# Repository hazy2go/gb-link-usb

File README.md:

<h1 align="center">gb-link-usb</h1>

<p align="center">
  <strong>Connect a Game Boy's link port to your computer over USB.</strong><br>
  Print from a real Game Boy straight to PNG, or watch live crypto prices from SODAX on it,<br>
  with a Raspberry Pi Pico 2 W and one cut link cable.
</p>

<p align="center">

</p>

<p align="center">
  <a href="#quick-start">Quick start</a> ·
  <a href="#printing">Printing</a> ·
  <a href="#sodax-on-the-game-boy">SODAX</a> ·
  <a href="#troubleshooting">Troubleshooting</a> ·
  <a href="#how-it-works">How it works</a> ·
  <a href="#roadmap">Roadmap</a>
</p>

---

## Highlights

- **A Game Boy Printer that saves PNGs.** The Pico answers exactly like Nintendo's printer, so games print as usual, and every picture lands on your computer.
- **Live SODAX market data on the Game Boy.** Prices, charts and real swap quotes from the [SODAX](https://sodax.com) API, drawn by our own Game Boy ROM.
- **No level shifter, no soldering.** The Pico 2's RP2350 pins tolerate the Game Boy's 5 V signals, so four wires on a breadboard are enough.
- **Double-click to use.** On a Mac, one launcher saves every print to `Pictures/GameBoy Prints`, with a sound. Any computer with Chrome or Edge can use the web page instead.
- **Tested and documented.** The printer logic and the decoder have automated tests, and every hardware step, measurement and bug is written down in the [logbook](docs/LOGBOOK.md).

## What you need

| | Part | Notes |
|---|---|---|
| 1 | **Raspberry Pi Pico 2 W** (or 2 WH) | Must be a Pico **2**. An original Pico (RP2040) is not 5 V tolerant and needs a level shifter. |
| 2 | **Game Boy link cable** you can cut | Built and tested with a DMG-04. You keep one plug end. |
| 3 | Breadboard and jumper wires | Or solder the four wires straight to the Pico. |
| 4 | Multimeter with continuity beep | To find which wire is which: colours are not standard. |
| 5 | Mac with [Node.js](https://nodejs.org), or any computer with Chrome/Edge | For saving the prints. |

## Quick start

### 1. Map the cable

Cut the link cable, keep one plug with some cable attached, and strip the wire ends. With the multimeter in beep mode, put a paperclip in one plug hole and touch each wire until it beeps.

| Plug pin | Signal | Pico pin |
|:---:|---|:---:|
| 5 | SCK, clock | **1** (GP0) |
| 2 | SOUT, data from the Game Boy | **2** (GP1) |
| 6 | GND | **3** (GND) |
| 3 | SIN, data to the Game Boy | **4** (GP2) |

Pins 1 (5 V) and 4 (SD) are usually not in the cable and are not needed. Leave the bare shield unconnected and taped.

### 2. Wire it to the Pico

<table>
  <tr>
    <td width="42%"></td>
    <td>
      <p>Press the Pico into the middle of the breadboard, USB end up. Each cable wire goes into a free hole in the same row as its Pico pin, on the left side of the gap.</p>
      <p>Nothing else is connected: no level shifter, no power wires.</p>
      <p>Hole-by-hole drawing: <a href="https://hazy2go.github.io/gb-link-usb/breadboard.html">interactive wiring page</a>.</p>
      <blockquote><strong>Power order matters.</strong> Plug the Pico into USB <em>before</em> switching the Game Boy on, and switch the Game Boy off <em>before</em> unplugging the Pico. The RP2350 tolerates 5 V on its pins only while it is powered.</blockquote>
    </td>
  </tr>
</table>

### 3. Flash the firmware

1. Get `gb_link_usb.uf2` from [Releases](../../releases), or [build it yourself](#development).
2. Hold the white **BOOTSEL** button on the Pico while plugging it into USB, then let go. A drive called **RP2350** appears.
3. Drag `gb_link_usb.uf2` onto the drive. The Pico restarts as a Game Boy Printer.

## Printing

### On a Mac: double-click

1. Download this repository (**Code → Download ZIP**) and unzip it.
2. Double-click **`GB Printer.command`**. The first time, macOS may block it: right-click it → **Open** → **Open**.
3. Wait for `Pico connected`, then print from the game.

Every print is saved in **Pictures → GameBoy Prints**, at original size and at 4×, with a sound. Unplugging and replugging the Pico is fine. Leave the window open while you print.

### Any computer: the web page

Open **<https://hazy2go.github.io/gb-link-usb/>** in Chrome or Edge, click **Connect Pico**, and print. Prints appear on the page with a PNG download link. Nothing to install.

<sub>To run it locally instead: `cd web && python3 -m http.server 8000`, then open http://localhost:8000.</sub>

## SODAX on the Game Boy

<p align="center"><sub>Emulator screenshots with live data. Tested on a real DMG.</sub></p>

Live prices, a 24H / 7D / 30D chart and a **real swap quote from the SODAX solver** for 9 coins (BTC, ETH, SOL, SODA, SUI, HYPE, AVAX, XLM, POL), on an original Game Boy.

1. Put `sodax.gb` (from [Releases](../../releases)) on a flash cart such as an EverDrive.
2. With the Pico on USB, double-click **`SODAX Bridge.command`** (or run `node tools/sodax-bridge.mjs`). Close the print tool first: one program uses the Pico at a time.
3. Switch the Game Boy on and start `sodax.gb`.

| Button | Action |
|---|---|
| ◄ ► (or ▲ ▼) | previous / next coin |
| B | time range: 24H, 7D, 30D |
| A or Start | load fresh data now (it also refreshes every 30 s) |

Prices come from the SODAX oracle (`/oracle/candles`), quotes from the SODAX solver (`/intent/quote`), no API key needed. How the Game Boy, the Pico's bridge mode and the PC talk: [`docs/SODAX.md`](docs/SODAX.md).

## Troubleshooting

| Problem | What to check |
|---|---|
| The game reports a printer error | Wiring: beep each plug pin to its Pico pin. If your colours were mapped wrong, swap the two data wires (plug pins 2 and 3). Power order: Pico first. |
| Stuck on `Waiting for the Pico...` | Is the printer firmware on the Pico? It should appear as **Pico** by Raspberry Pi. Try another USB cable, some are charge-only. |
| A print did not save | See `gbprint.log` in the prints folder. Raw data of every session is kept in `raw/`; `node tools/render.mjs <file>` turns it into PNGs. |
| SODAX screen stays on "waiting" | Is the bridge window open and saying "bridge mode on"? Is the Pico on firmware v0.2.0 or newer? Press A to request a screen. |
| The web page cannot connect | Use Chrome or Edge on a desktop (Safari and Firefox have no Web Serial). Close the Mac tool first: only one program can use the Pico at a time. |

## How it works

```
Game Boy link port ──► Pico 2 W ──────────────────────────────────────► computer
 5 V, clocked serial    PIO follows the Game Boy's clock (glitch filter)    gbprint.mjs or the web page
                        core 1: answers like a Game Boy Printer             decodes packets → PNG
                        core 0: streams every byte over USB serial
```

- **Link layer.** A PIO state machine is the clock *slave*: it outputs a bit when the Game Boy's clock falls and samples the Game Boy's bit when it rises. A 1.6 µs glitch filter rejects crosstalk from the data line, which otherwise shows up as extra clock edges.
- **Printer.** [`firmware/src/printer.c`](firmware/src/printer.c) replies `0x00` to every byte, then the printer ID `0x81` and a status byte, and walks through the same status sequence as a real printer (busy while "printing", then ready). Replies are queued two bytes ahead, matching how the PIO loads them.
- **Decoding.** [`web/gbprinter.js`](web/gbprinter.js) parses packets, checks checksums, expands compressed data, turns 2-bit tiles into pixels and applies the print palette. The same file runs in the browser and in the Mac tool.

*Right: a test image sent through the full printer protocol and decoded by that code.*

<br clear="right">

## Project layout

```
firmware/         Pico 2 W firmware (C, Pico SDK): PIO link, printer emulator, USB serial
  test/           host tests for the printer state machine
  firstlight/     patch used to run stacksmashing's firmware for the first wiring test
web/              decoder library + web page (Web Serial)
tools/            gbprint.mjs (Mac print tool), sodax-bridge.mjs + sodax.mjs (SODAX data),
                  render.mjs, printcap.py, linktest.py
rom/              Game Boy ROMs (RGBDS): sodax.gb, linktest.gb, printtest.gb; mkfont.py makes the font
hw/              own PCB (KiCad, rev A ready to order), case, scripted build + checks
sim/link/        ngspice simulation of the link lines
docs/             PROTOCOL.md, PLAN.md, PCB.md, LOGBOOK.md, breadboard drawing, images
GB Printer.command    double-click launcher for the Mac print tool
SODAX Bridge.command  double-click launcher for SODAX on the Game Boy
```

## Development

```sh
# firmware (needs the Arm GNU toolchain and Pico SDK 2.3.1; PICO_SDK_PATH set)
cmake -S firmware -B firmware/build -G Ninja && ninja -C firmware/build   # → firmware/build/gb_link_usb.uf2

# tests
make -C firmware/test        # printer state machine (host, with sanitizers)
cd web && npm test           # decoder

# Game Boy ROMs (RGBDS)
make -C rom
node tools/sodax-bridge.mjs --dry   # print live SODAX screens without hardware
```

`rom/printtest.gb` makes the Game Boy act like a printing game and shows on screen what the printer answers (`… 81 00` is correct). `rom/linktest.gb` echoes bytes for testing the link in the other direction. Details: [`firmware/README.md`](firmware/README.md).

## Roadmap

- [x] Wiring and first link test: 1,000 bytes both ways, 0 errors
- [x] Game Boy Printer emulator: prints from a DMG saved as PNG
- [ ] More printer games tested (compressed and multi-part prints)
- [x] General PC link: live SODAX market data on the Game Boy (bridge mode)
- [ ] Online link play between two Game Boys
- [ ] Own small PCB with USB-C and a case, so nobody has to cut a cable: rev A designed and checked ([hw/](hw/README.md)), not ordered yet

## Credits

- [Pan Docs](https://gbdev.io/pandocs/): link port and printer documentation.
- [mofosyne/arduino-gameboy-printer-emulator](https://github.com/mofosyne/arduino-gameboy-printer-emulator): the reference printer emulator. Our printer status behaviour follows it; the code is our own.
- [stacksmashing/gb-link-firmware](https://github.com/stacksmashing/gb-link-firmware): Pico link firmware, used with a small patch for the first wiring test.
- [SODAX](https://sodax.com): market data API and the official logo used on the splash screen (from [gosodax/sodax-sdks](https://github.com/gosodax/sodax-sdks), MIT).
- [HerrZatacke/gb-printer-web](https://github.com/HerrZatacke/gb-printer-web) and [Raphael-Boichot/The-TinyGB-Printer](https://github.com/Raphael-Boichot/The-TinyGB-Printer): prior art for printer images.

Sister project: [WiFi Game Boy Cartridge](https://github.com/hazy2go/wifi-game-boy-cartridge).

## License

[MIT](LICENSE). Exception: `firmware/firstlight/` patches GPL-3.0 code and is GPL-3.0.

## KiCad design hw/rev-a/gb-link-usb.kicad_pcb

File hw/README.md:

# Hardware: PCB rev A

A small USB-C dongle with the Game Boy link cable soldered on. RP2350A core from Raspberry Pi's minimal design, three 74LVC1T45 translators running the Game Boy side at USB 5 V (safe in any power order), ESD on USB and on the link lines. 34.2 x 63.7 mm, 2 layers, all parts on top, assembled by JLC. Spec and part choice: [`docs/PCB.md`](../docs/PCB.md). **Not ordered yet:** see [`rev-a/fab/ORDER.md`](rev-a/fab/ORDER.md).

Gerbers as the fab sees them (rendered independently with tracespace, top and bottom):

## Files
- `rev-a/`: KiCad 10 project. `link.json` is the source of the Link sheet (USB-C, buffers, ESD, cable pads, LED); the root sheet is Raspberry Pi's minimal design, edited by script.
- `rev-a/fab/`: order files (Gerbers zip, BOM, CPL) and the check reports.
- `case/`: 3D-printable case (OpenSCAD).
- `reference/RPI-RP2350A-MINIMAL_R4-S1_public/`: Raspberry Pi RP2350A minimal design (MIT, see its LICENSE.txt), the base for our board.
- `../sim/link/`: ngspice simulation of the link lines (why the series resistors are 220R with 100 pF).

## Rebuild everything (scripted, from the untouched RPi design)
KPY = KiCad's Python (`/Applications/KiCad/KiCad.app/Contents/Frameworks/Python.framework/Versions/Current/bin/python3`).
```sh
$KPY hw/tools/add_sheet.py          # schematic: root from RPi's design + Link sheet from link.json
$KPY hw/tools/extract_libs.py       # RPi symbols/footprints into project libraries
$KPY hw/tools/pcb_build.py          # board: RPi layout, new outline, our parts placed
$KPY hw/tools/pcb_route.py hand     # hand routes (GPIO fan, DIR lines)
$KPY hw/tools/pcb_gnd.py            # a GND via for every new GND pad
$KPY hw/tools/pcb_route.py 60       # Freerouting (retries until DRC is clean) + tidy-up + zone fill
hw/tools/make_fab.sh                # Gerbers, drill, BOM + check, CPL + check, pin audit
```

## Checks (all scripted, results 2026-10-16)
| check | tool | result |
|---|---|---|
| ERC | kicad-cli | same as Raspberry Pi's untouched design (2 off-grid, 1 power pin pair, 2 regulator pins) |
| DRC + schematic parity | kicad-cli | 0 errors, 0 warnings, 0 unconnected, parity 0 |
| Routing tidy-up | `route_audit.py` / `route_clean.py` | no stubs, sharp angles or pointless vias (one harmless detour on B_SI); a few sub-0.05 mm pad-entry jogs left (most in RPi's own routing, kept as drawn) |
| Part heights | `height_check.py` | tallest: USB-C 3.25 mm, buttons 2.5 mm (feeds the case) |
| Link signals | `sim/link/run_sim.py` | 0 of 72 runs over a limit or glitching with 220R + 100 pF (SIN: 1k, also clean) |
| Independent review | fresh agent, datasheets only | no wiring defect; findings fixed or listed (LOGBOOK 2026-10-16) |
| BOM vs JLC | `make_bom.py` | all parts exist, match footprint and value; 1 stock FAIL: L1 inductor (hold point) |
| Placement | `make_cpl.py` | all 57 parts matched pad by pad against JLC's footprints |
| Pins | `pin_audit.py` | every pin vs JLC's symbol; caught the LED's reversed pad numbering (fixed in the CPL) |
| Gerbers | tracespace | render above |

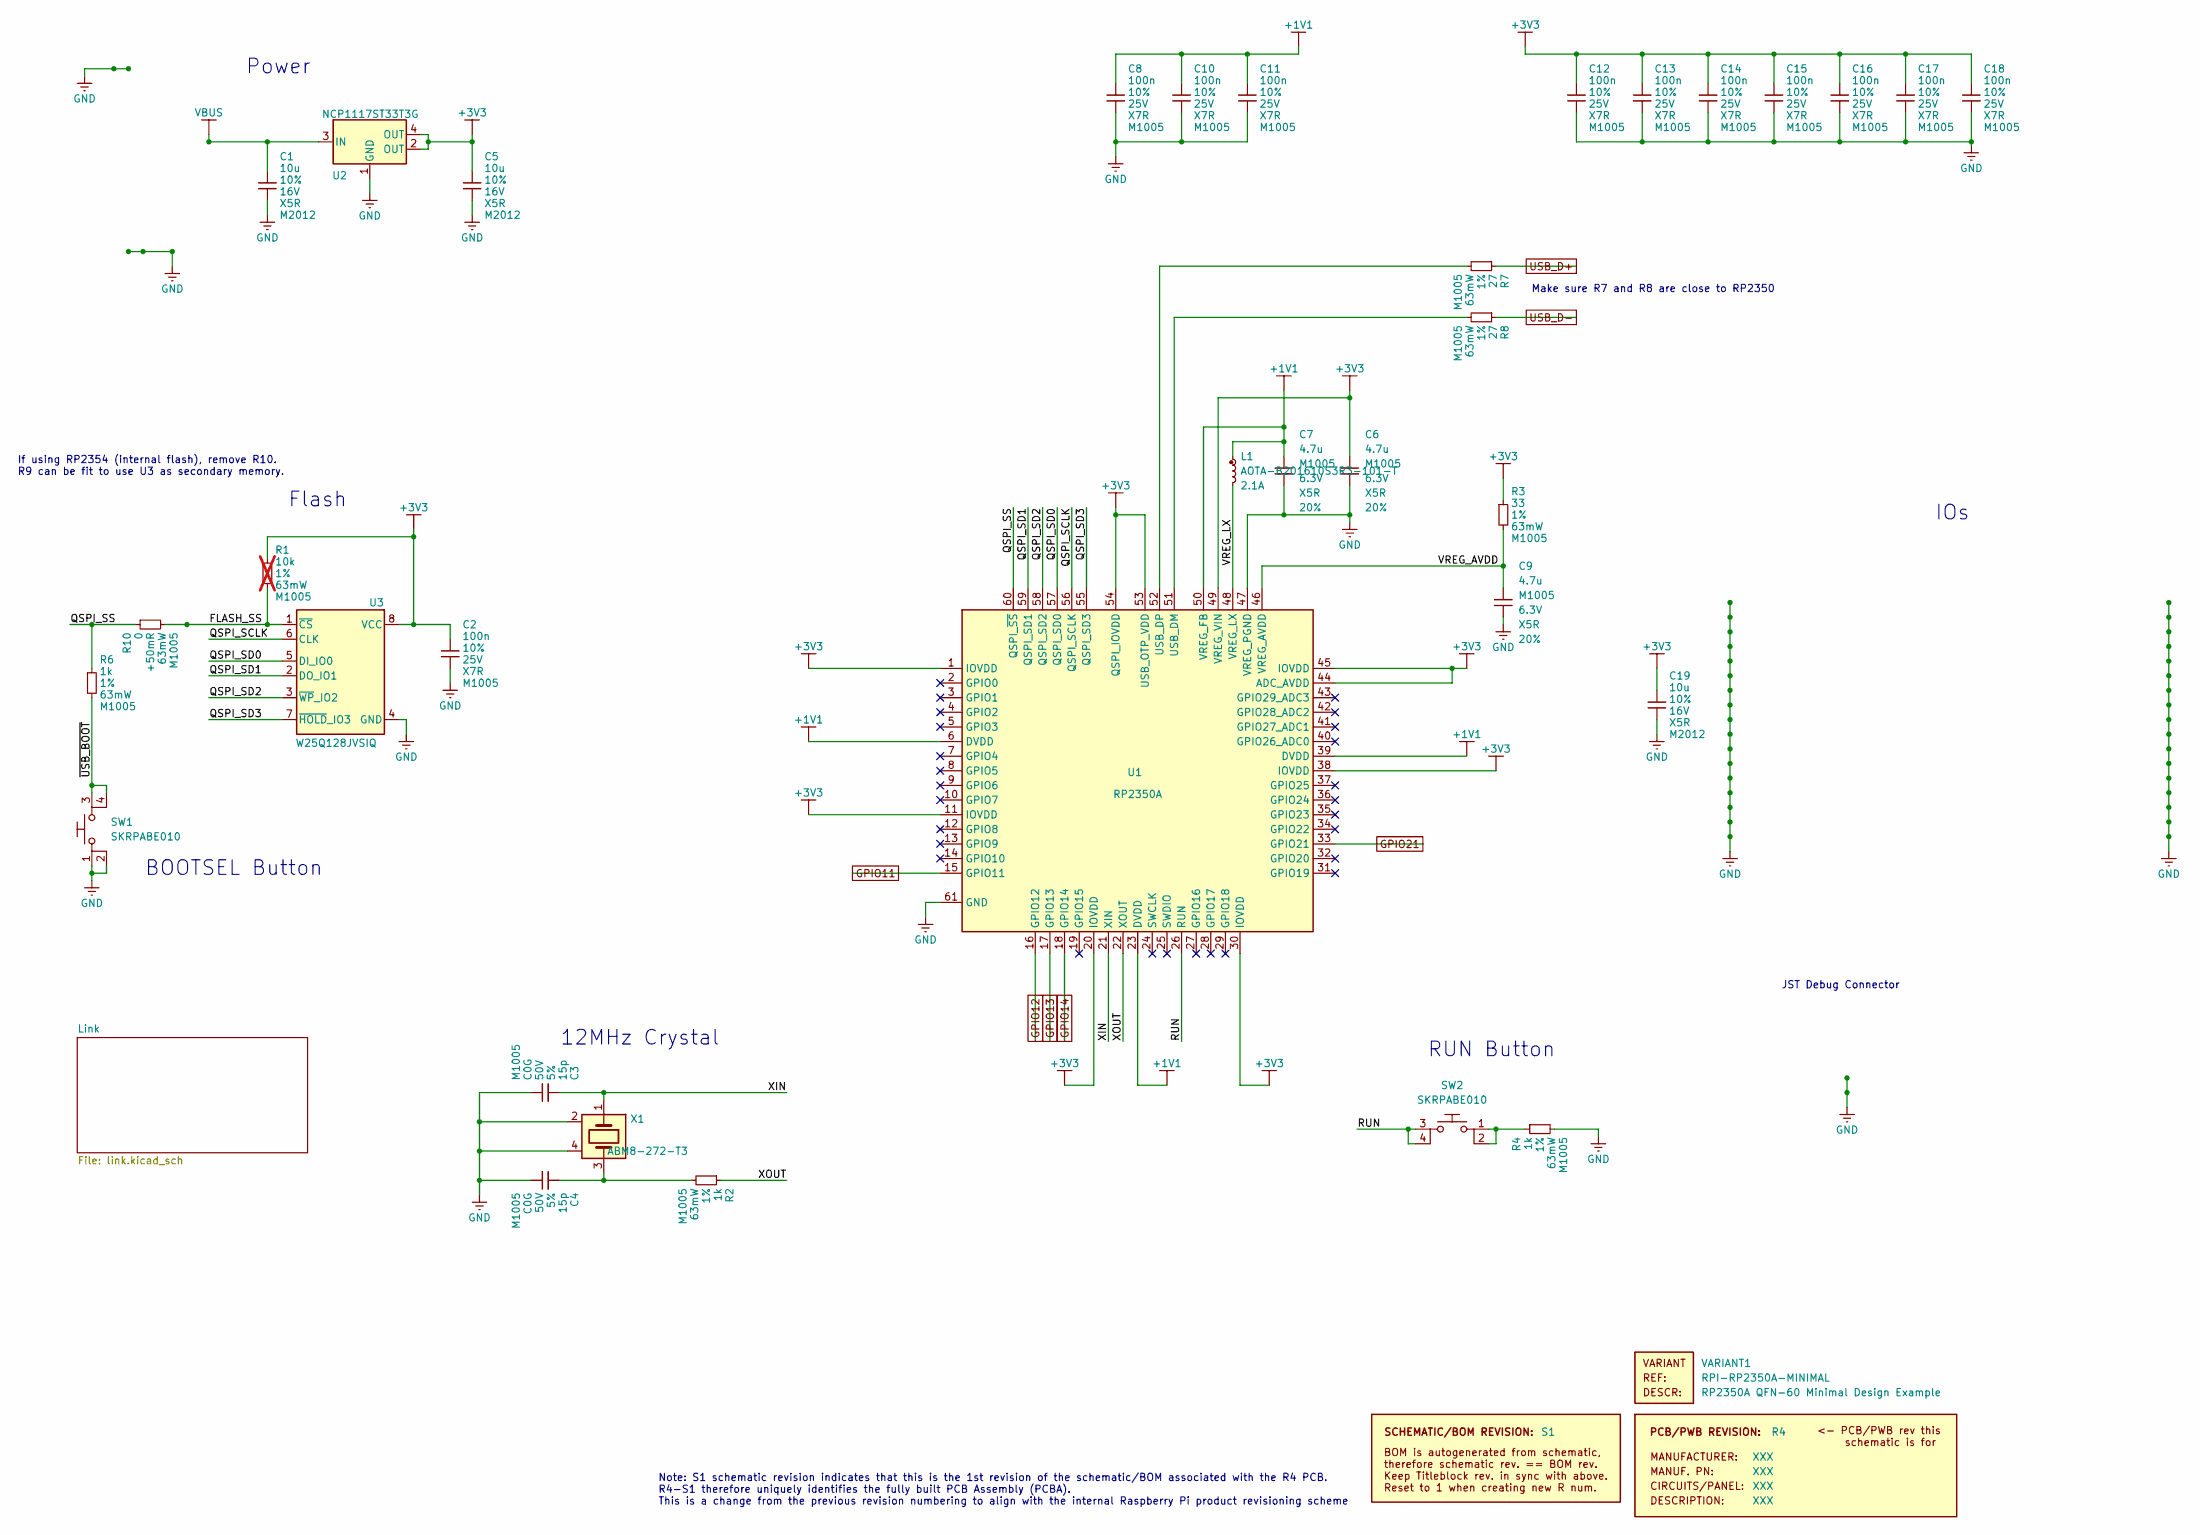
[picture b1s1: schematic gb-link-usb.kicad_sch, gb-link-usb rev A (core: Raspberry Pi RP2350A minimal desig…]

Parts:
C1, C5, C19: 10u; generic_capc2012x125; voltage 16V; tolerance 10%; part_uid RP-01GYSK-AVBE41; LCSC C15850
C2, C8, C10, C11, C12, C13, C14, C15, C16, C17, C18: 100n; generic_capc1005x50; voltage 25V; tolerance 10%; part_uid RP-01BJ9Y-KRGF41; LCSC C1525
C3, C4: 15p; generic_capc1005x50; voltage 50V; tolerance 5%; part_uid RP-01C89W-LLY9XV; LCSC C1548
C6, C7: 4.7u; generic_capc1005x50_wide; voltage 6.3V; tolerance 20%; part_uid RP-019A1P-0C2GHY; LCSC C23733
C9: 4.7u; generic_capc1005x50; voltage 6.3V; tolerance 20%; part_uid RP-019A1P-0C2GHY; LCSC C23733
L1: AOTA-B201610S3R3-101-T; abracon_aota-b201610s3r3-101-t; tolerance 20%; part_uid RP-01GY5D-2VC7WP; LCSC C42411119
PCB1: R4; manufacturer_pn XXX
R1: 10k; generic_resc1005x35; tolerance 1%; voltage 50V; part_uid RP-019A1P-53DHSX; LCSC C25744; not fitted
R2, R4, R6: 1k; generic_resc1005x35; tolerance 1%; voltage 50V; part_uid RP-019A1P-4Z6ZWY; LCSC C11702
R3: 33; generic_resc1005x35; tolerance 1%; voltage 50V; part_uid RP-019A1P-58PW9L; LCSC C25105
R7, R8: 27; generic_resc1005x35; tolerance 1%; voltage 50V; part_uid RP-01C89V-LTEYC4; LCSC C25100
R10: 0; generic_resc1005x35; tolerance +50mR; voltage 50V; part_uid RP-019A1P-4Y4V63; LCSC C17168
SBREV1: S1
SW1, SW2: SKRPABE010; wurthelek_434133025816; part_uid RP-01H0MT-6E9H8F; LCSC C115360
U1: RP2350A; rpi_rp2350a_vias; part_uid RP-01HA9H-9K5E8T; LCSC C42411118
U2: NCP1117ST33T3G; onsemi_ncp1117st33t3g; voltage 3.3V; part_uid RP-01JWD9-7JRX6J; LCSC C26537
U3: W25Q128JVSIQ; generic_soic127p790x195-8; voltage 2.7-3.6V; part_uid RP-01JWD4-F1H4N9; LCSC C97521
VARIANT1: RPI-RP2350A-MINIMAL
X1: ABM8-272-T3; generic_xtalcc320x250x80-4; tolerance 30ppm; part_uid RP-01G8X7-GS352B; LCSC C20625731

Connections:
+1V1: C7.1, C8.1, C10.1, C11.1, L1.1, U1.6 (DVDD), U1.23 (DVDD), U1.39 (DVDD), U1.50 (VREG_FB)
+3V3: C2.1, C5.1, C6.1, C12.1, C13.1, C14.1, C15.1, C16.1, C17.1, C18.1, C19.1, R1.1, R3.1, U1.1 (IOVDD), U1.11 (IOVDD), U1.20 (IOVDD), U1.30 (IOVDD), U1.38 (IOVDD), U1.44 (ADC_AVDD), U1.45 (IOVDD), U1.49 (VREG_VIN), U1.53 (USB_OTP_VDD), U1.54 (QSPI_IOVDD), U2.2 (OUT), U2.4 (OUT), U3.8 (VCC); also elsewhere on the board
/FLASH_SS: R1.2, R10.2, U3.1 (~CS)
/QSPI_SCLK: U1.56 (QSPI_SCLK), U3.6 (CLK)
/QSPI_SD0: U1.57 (QSPI_SD0), U3.5 (DI_IO0)
/QSPI_SD1: U1.59 (QSPI_SD1), U3.2 (DO_IO1)
/QSPI_SD2: U1.58 (QSPI_SD2), U3.3 (~WP_IO2)
/QSPI_SD3: U1.55 (QSPI_SD3), U3.7 (~HOLD_IO3)
/QSPI_SS: R6.1, R10.1, U1.60 (QSPI_~SS)
/RUN: SW2.3, SW2.4, U1.26 (RUN)
/VREG_AVDD: C9.1, R3.2, U1.46 (VREG_AVDD)
/VREG_LX: L1.2, U1.48 (VREG_LX)
/XIN: C3.1, U1.21 (XIN), X1.1
/XOUT: R2.1, U1.22 (XOUT)
/~USB_BOOT: R6.2, SW1.3, SW1.4
GND: C1.2, C2.2, C3.2, C4.2, C5.2, C6.2, C7.2, C8.2, C9.2, C10.2, C11.2, C12.2, C13.2, C14.2, C15.2, C16.2, C17.2, C18.2, C19.2, R4.2, SW1.1, SW1.2, U1.47 (VREG_PGND), U1.61 (GND), U2.1 (GND), U3.4 (GND), X1.2, X1.4; also elsewhere on the board
GPIO11: U1.15 (GPIO11); also elsewhere on the board
GPIO12: U1.16 (GPIO12); also elsewhere on the board
GPIO13: U1.17 (GPIO13); also elsewhere on the board
GPIO14: U1.18 (GPIO14); also elsewhere on the board
GPIO21: U1.33 (GPIO21); also elsewhere on the board
unnamed: C4.1, R2.2, X1.3
unnamed: R4.1, SW2.1, SW2.2
unnamed: R8.2, U1.51 (USB_DM)
unnamed: R7.2, U1.52 (USB_DP)
USB_D+: R7.1; also elsewhere on the board
USB_D-: R8.1; also elsewhere on the board
VBUS: C1.1, U2.3 (IN); also elsewhere on the board

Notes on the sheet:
JST Debug Connector
IOs
RUN Button
BOOTSEL Button
If using RP2354 (internal flash), remove R10. R9 can be fit to use U3 as secondary memory.
Flash
Note: S1 schematic revision indicates that this is the 1st revision of the schematic/BOM associated with the R4 PCB. R4-S1 therefore uniquely identifies the fully built PCB Assembly (PCBA). This is a change from the previous revision numbering to align with the internal Raspberry Pi product revisio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
Make sure R7 and R8 are close to RP2350
12MHz Crystal
Power

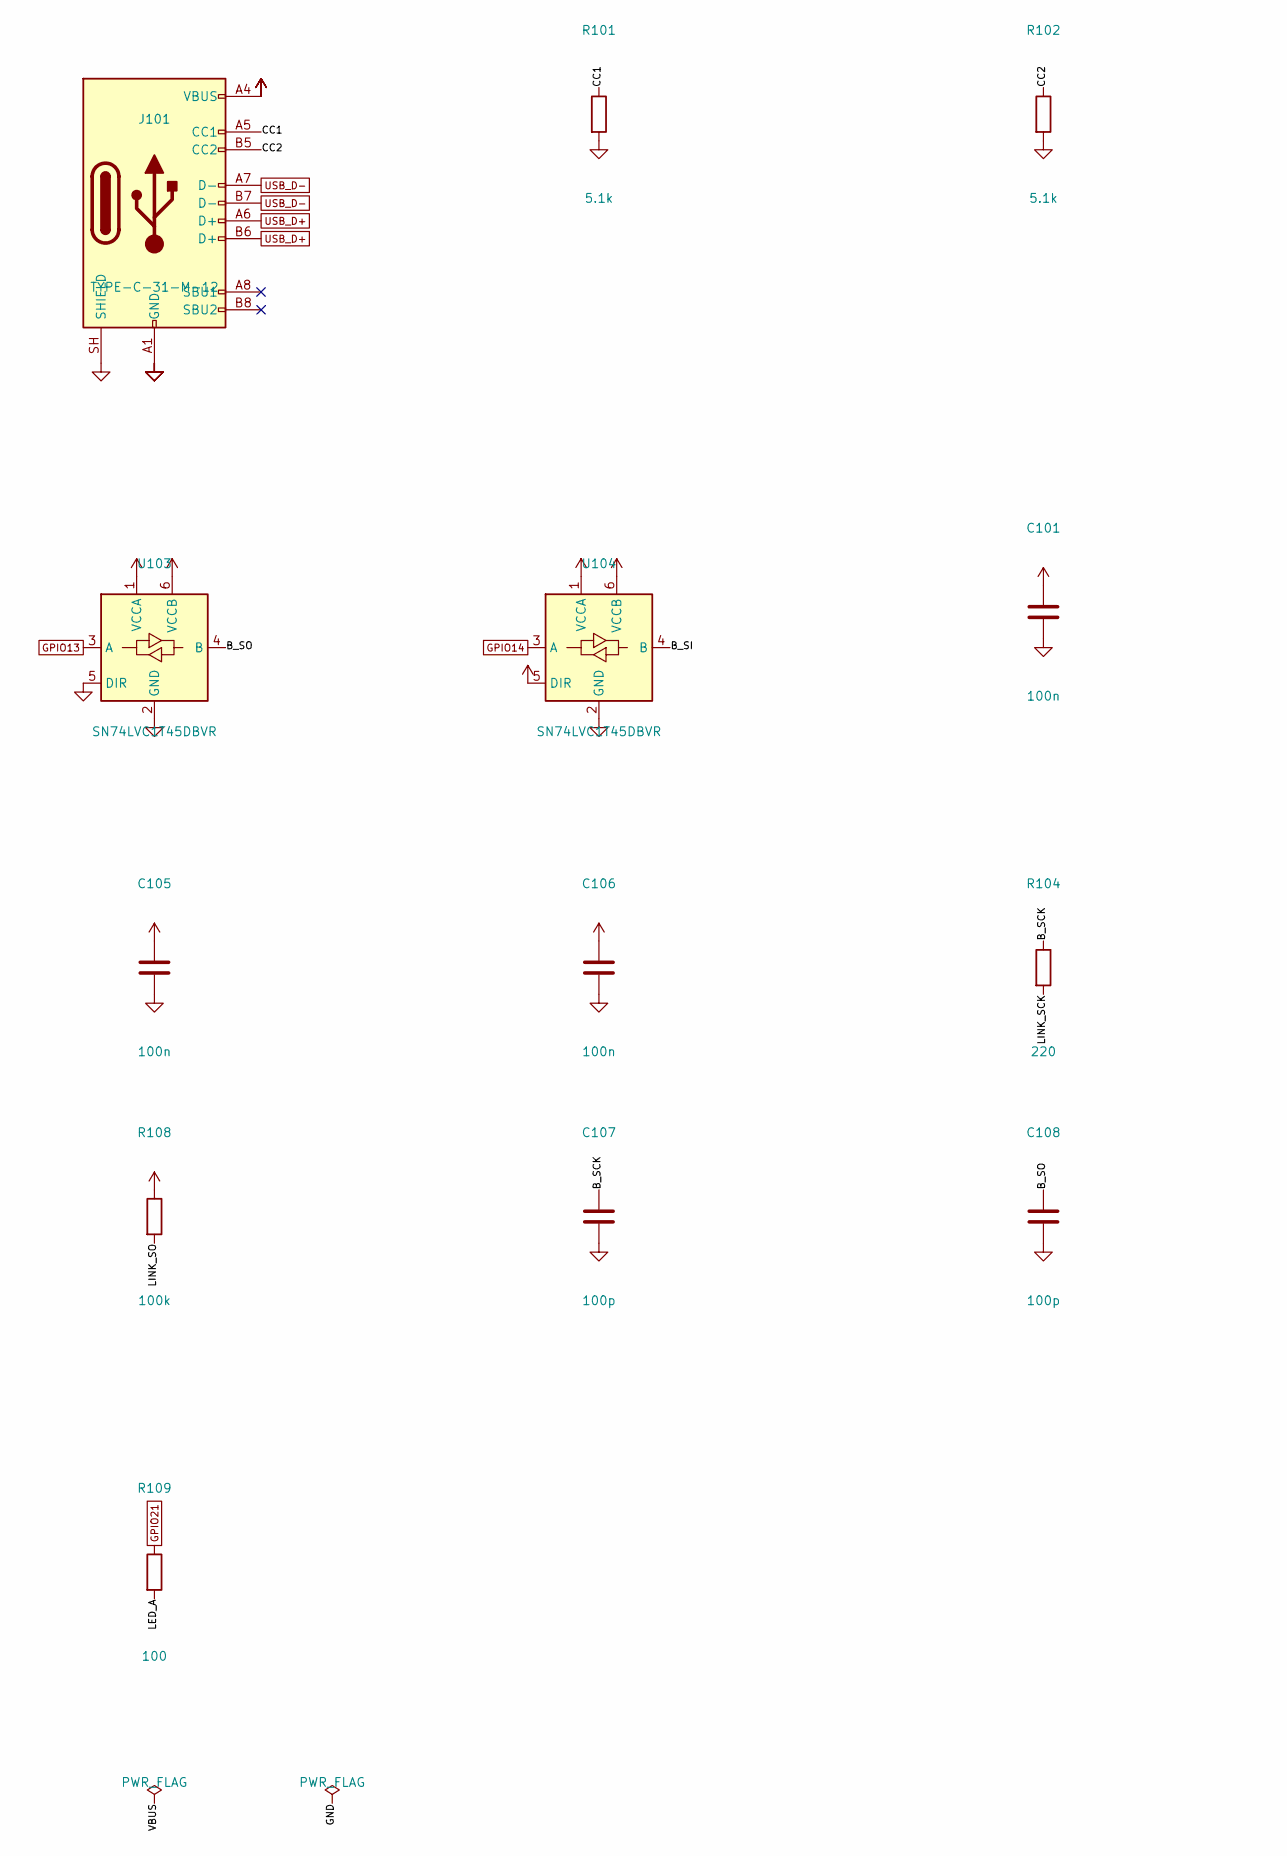
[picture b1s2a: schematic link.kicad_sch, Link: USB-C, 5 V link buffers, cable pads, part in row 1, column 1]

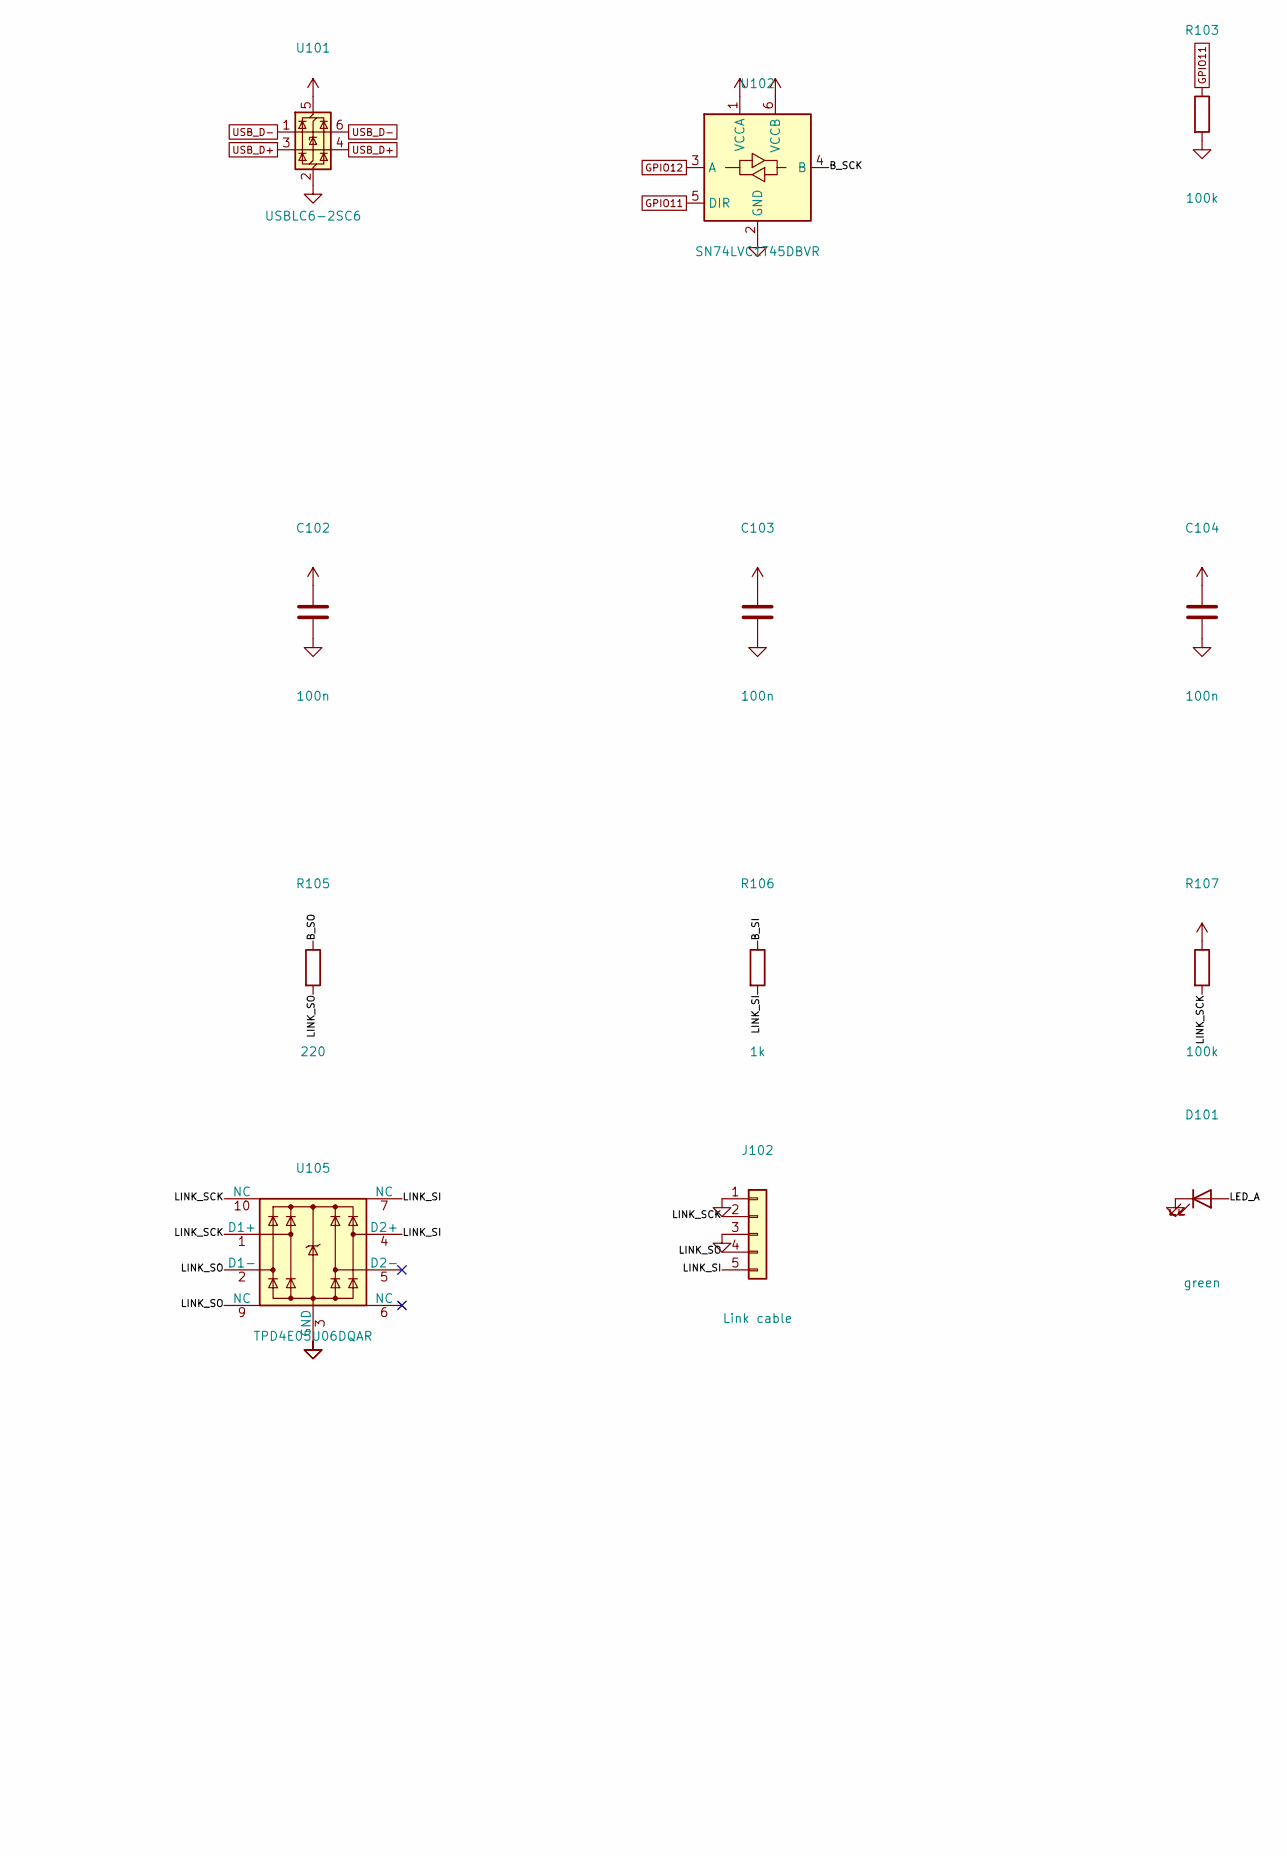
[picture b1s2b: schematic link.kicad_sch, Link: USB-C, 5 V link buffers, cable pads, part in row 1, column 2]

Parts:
C101, C102, C103, C104, C105, C106: 100n; C_0402_1005Metric; LCSC C1525
C107, C108: 100p; C_0402_1005Metric; LCSC C1546
D101: green; LED_0805_2012Metric; LCSC C2297
J101: TYPE-C-31-M-12; USB_C_Receptacle_HRO_TYPE-C-31-M-12_Flush; LCSC C165948
J102: Link cable; SolderWire-0.15sqmm_1x05_P4mm_D0.5mm_OD1.5mm_Relief
R101, R102: 5.1k; R_0402_1005Metric; LCSC C25905
R103, R107, R108: 100k; R_0402_1005Metric; LCSC C25741
R104, R105: 220; R_0402_1005Metric; LCSC C25091
R106: 1k; R_0402_1005Metric; LCSC C11702
R109: 100; R_0402_1005Metric; LCSC C25076
U101: USBLC6-2SC6; SOT-23-6; LCSC C7519
U102, U103, U104: SN74LVC1T45DBVR; SOT-23-6; LCSC C7843
U105: TPD4E05U06DQAR; USON-10_2.5x1.0mm_P0.5mm; LCSC C138714

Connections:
+3V3: C101.1, C103.1, C105.1, U102.1 (VCCA), U103.1 (VCCA), U104.1 (VCCA), U104.5 (DIR); also elsewhere on the board
/Link/B_SCK: C107.1, R104.1, U102.4 (B)
/Link/B_SI: R106.1, U104.4 (B)
/Link/B_SO: C108.1, R105.1, U103.4 (B)
/Link/CC1: J101.A5 (CC1), R101.1
/Link/CC2: J101.B5 (CC2), R102.1
/Link/LED_A: D101.2 (A), R109.2
/Link/LINK_SCK: J102.2, R104.2, R107.2, U105.1 (D1+), U105.10 (NC)
/Link/LINK_SI: J102.5, R106.2, U105.4 (D2+), U105.7 (NC)
/Link/LINK_SO: J102.4, R105.2, R108.2, U105.2 (D1-), U105.9 (NC)
GND: C101.2, C102.2, C103.2, C104.2, C105.2, C106.2, C107.2, C108.2, D101.1 (K), J101.A1 (GND), J101.A12 (GND), J101.B1 (GND), J101.B12 (GND), J101.SH (SHIELD), J102.1, J102.3, R101.2, R102.2, R103.2, U101.2 (GND), U102.2 (GND), U103.2 (GND), U103.5 (DIR), U104.2 (GND), U105.3 (GND), U105.8 (GND); also elsewhere on the board
GPIO11: R103.1, U102.5 (DIR); also elsewhere on the board
GPIO12: U102.3 (A); also elsewhere on the board
GPIO13: U103.3 (A); also elsewhere on the board
GPIO14: U104.3 (A); also elsewhere on the board
GPIO21: R109.1; also elsewhere on the board
USB_D+: J101.A6 (D+), J101.B6 (D+), U101.3 (I/O2), U101.4 (I/O2); also elsewhere on the board
USB_D-: J101.A7 (D-), J101.B7 (D-), U101.1 (I/O1), U101.6 (I/O1); also elsewhere on the board
VBUS: C102.1, C104.1, C106.1, J101.A4 (VBUS), J101.A9 (VBUS), J101.B4 (VBUS), J101.B9 (VBUS), R107.1, R108.1, U101.5 (VBUS), U102.6 (VCCB), U103.6 (VCCB), U104.6 (VCCB); also elsewhere on the board

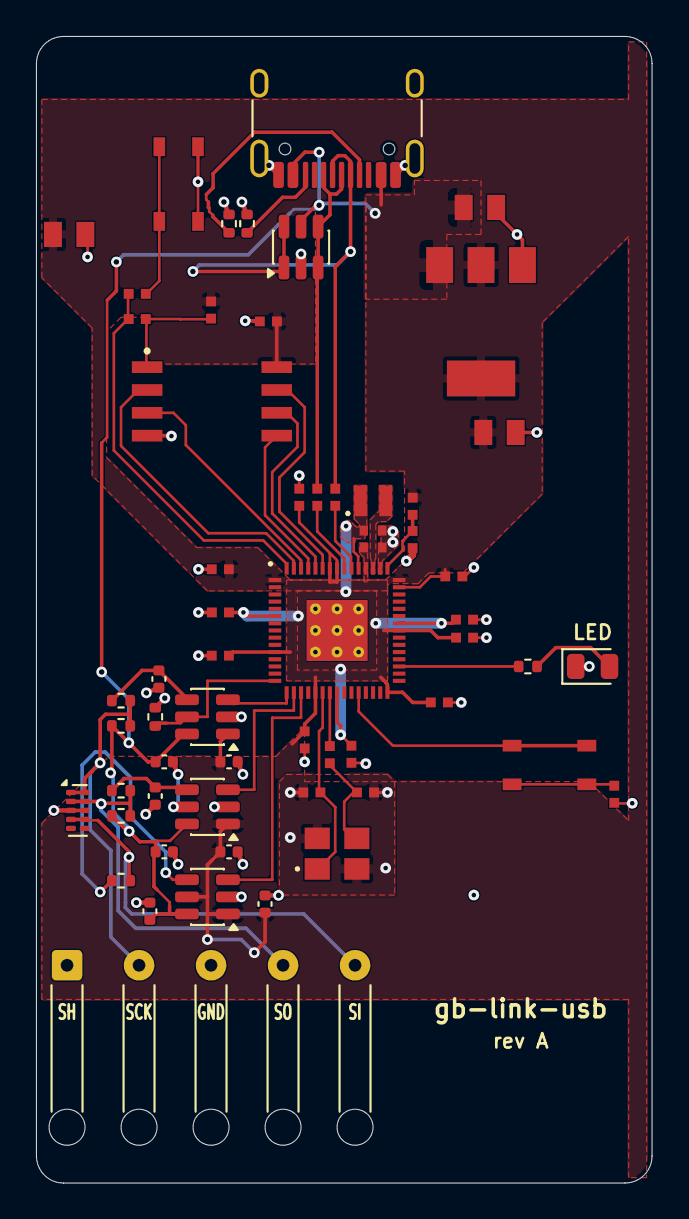
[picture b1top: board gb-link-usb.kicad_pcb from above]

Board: 2 copper layers, 34.2 x 63.7 mm, 59 parts (0 on the bottom side), 37 nets.

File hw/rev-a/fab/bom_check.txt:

BOM check for 5 boards: 27 lines, 57 placed parts, 10 extended parts (feeder fee each), DNP: R1

ok   C15850    base   stock   3657249 need   20  10u                C1,C5,C19                                CL21A106KAYNNNE        
ok   C1525     base   stock  22403876 need   60  100n               C2,C8,C10,C11,C12,C13,C14,C15,C16,C17,C1 CL05B104KO5NNNC        
ok   C1548     base   stock   1209694 need   15  15p                C3,C4                                    0402CG150J500NT        
ok   C23733    base   stock   1859380 need   15  4.7u               C6,C7                                    CL05A475MP5NRNC        
ok   C23733    base   stock   1859380 need   10  4.7u               C9                                       CL05A475MP5NRNC        
ok   C1525     base   stock  22403876 need   35  100n               C101,C102,C103,C104,C105,C106            CL05B104KO5NNNC        
ok   C1546     base   stock   3945135 need   15  100p               C107,C108                                0402CG101J500NT        
ok   C2297     base   stock   2716005 need   10  green              D101                                     KT-0805G               
ok   C165948   expand stock    379998 need   10  TYPE-C-31-M-12     J101                                     TYPE-C-31-M-12         
FAIL C42411119 expand stock         9 need   10  AOTA-B201610S3R3-1 L1                                       AOTA-B201610S3R3-101-T STOCK 9 < 10
ok   C11702    base   stock  14390861 need   20  1k                 R2,R4,R6                                 0402WGF1001TCE         
ok   C25105    base   stock   1423784 need   10  33                 R3                                       0402WGF330JTCE         
ok   C25100    expand stock     33133 need   15  27                 R7,R8                                    0402WGF270JTCE         
ok   C17168    base   stock   9266226 need   10  0                  R10                                      0402WGF0000TCE         
ok   C25905    base   stock   5299091 need   15  5.1k               R101,R102                                0402WGF5101TCE         
ok   C25741    base   stock   9728792 need   20  100k               R103,R107,R108                           0402WGF1003TCE         
ok   C25091    base   stock   1296840 need   15  220                R104,R105                                0402WGF2200TCE         
ok   C11702    base   stock  14390861 need   10  1k                 R106                                     0402WGF1001TCE         
ok   C25076    base   stock   8294192 need   10  100                R109                                     0402WGF1000TCE         
ok   C115360   expand stock     33840 need   15  SKRPABE010         SW1,SW2                                  SKRPABE010             
ok   C42411118 expand stock      6312 need   10  RP2350A            U1                                       RP2350A                
ok   C26537    expand stock     61140 need   10  NCP1117ST33T3G     U2                                       NCP1117ST33T3G         
ok   C97521    base   stock     66926 need   10  W25Q128JVSIQ       U3                                       W25Q128JVSIQ           
ok   C7519     expand stock     48218 need   10  USBLC6-2SC6        U101                                     USBLC6-2SC6            
ok   C7843     expand stock    348745 need   20  SN74LVC1T45DBVR    U102,U103,U104                           SN74LVC1T45DBVR        
ok   C138714   expand stock    247062 need   10  TPD4E05U06DQAR     U105                                     TPD4E05U06DQAR         
ok   C20625731 expand stock      6186 need   10  ABM8-272-T3        X1                                       ABM8-272-T3            

RESULT: 1 FAIL

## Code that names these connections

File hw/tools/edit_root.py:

#!/usr/bin/env python3
"""Turn Raspberry Pi's RP2350A minimal schematic into our root sheet (idempotent on the original file).

- removes the connectors we don't use (micro-USB J1, headers J2/J3, SWD J4), R9 (optional
  second-memory link on GPIO0, which is our SCK pin) and the mounting holes MH1-4
- removes wires and labels left dangling by that, repeatedly
- unused GPIOs: label + stub removed, a no-connect flag on the RP2350 pin
- signals used by the Link sheet become global labels
- JLC part numbers (LCSC field) for the RPi core parts (LOGBOOK 2026-10-16: JLC stock, RPi's part advice)
Usage: edit_root.py IN.kicad_sch OUT.kicad_sch
"""
import sys, uuid
from sexp import parse, dump, find, first, Str
from schgeom import symbol_pins

REMOVE = {'J1', 'J2', 'J3', 'J4', 'R9', 'MH1', 'MH2', 'MH3', 'MH4'}   # MH: mounting holes, the dongle has none
GLOBAL = {'GPIO11', 'GPIO12', 'GPIO13', 'GPIO14', 'GPIO21', 'USB_D+', 'USB_D-'}
# LCSC numbers for the core parts, checked on JLC 2026-10-16 (hw/tools/jlc_search.py). (value, lcsc)
# None keeps RPi's value. RPi's hardware design guide asks for exactly the ABM8-272-T3 crystal and the
# polarity-marked AOTA-B201610S3R3-101-T inductor; both kept.
LCSC = {
    'U1': (None, 'C42411118'), 'U2': (None, 'C26537'), 'U3': (None, 'C97521'),
    'X1': ('ABM8-272-T3', 'C20625731'), 'L1': ('AOTA-B201610S3R3-101-T', 'C42411119'),
    'SW1': ('SKRPABE010', 'C115360'), 'SW2': ('SKRPABE010', 'C115360'),   # Wurth 434133025816 out of stock; Alps J-lead 4.2x3.2, 1.6 N like the Wurth
    'C1': (None, 'C15850'), 'C5': (None, 'C15850'), 'C19': (None, 'C15850'),          # 10u 0805 25 V X5R
    'C3': (None, 'C1548'), 'C4': (None, 'C1548'),                                      # 15p 0402 C0G
    'C6': (None, 'C23733'), 'C7': (None, 'C23733'), 'C9': (None, 'C23733'),            # 4.7u 0402 6.3 V X5R
    'R1': (None, 'C25744'), 'R2': (None, 'C11702'), 'R4': (None, 'C11702'), 'R6': (None, 'C11702'),
    'R3': (None, 'C25105'), 'R7': (None, 'C25100'), 'R8': (None, 'C25100'), 'R10': (None, 'C17168'),
}
LCSC.update({f'C{n}': (None, 'C1525') for n in (2, 8, 10, 11, 12, 13, 14, 15, 16, 17, 18)})   # 100n 0402 X7R 16 V
NOT_PARTS = {'PCB1', 'SBREV1', 'VARIANT1'}    # RPi's BOM directive symbols: not placed parts
_NS = uuid.UUID('9b1c7e30-2f4a-4c8e-8d1b-6a5f0e2c3d47')
_n = [0]


def U():
    _n[0] += 1
    return Str(str(uuid.uuid5(_NS, f'nc/{_n[0]}')))


def P(xy):
    return (round(float(xy[1]), 3), round(float(xy[2]), 3))


def ref_of(inst):
    return next((str(p[2]) for p in find(inst, 'property') if p[1] == 'Reference'), '?')


def on_segment(p, a, b):
    (x, y), (x1, y1), (x2, y2) = p, a, b
    if abs((x2 - x1) * (y - y1) - (y2 - y1) * (x - x1)) > 1e-6:
        return False
    return min(x1, x2) - 1e-6 <= x <= max(x1, x2) + 1e-6 and min(y1, y2) - 1e-6 <= y <= max(y1, y2) + 1e-6


def main(src, dst):
    sch = parse(open(src).read())
    pins_all = symbol_pins(sch)
    sch[:] = [c for c in sch if not (isinstance(c, list) and c[0] == 'symbol' and ref_of(c) in REMOVE)]
    pins = {k: v for k, v in pins_all.items() if k[0] not in REMOVE}
    pin_pts = set(pins.values())

    # iterative dangling cleanup
    while True:
        wires = [c for c in sch if isinstance(c, list) and c[0] == 'wire']
        segs = [(w, [P(xy) for xy in find(first(w, 'pts'), 'xy')]) for w in wires]
        labels = [c for c in sch if isinstance(c, list) and c[0] in ('label', 'global_label')]
        lab_pts = {P(first(l, 'at')) for l in labels}
        junc = {P(first(j, 'at')) for j in find(sch, 'junction')}
        nc = {P(first(j, 'at')) for j in find(sch, 'no_connect')}

        def connected(pt, me):
            if pt in pin_pts or pt in lab_pts or pt in junc or pt in nc:
                return True
            for w, (a, b) in segs:
                if w is not me and (pt in (a, b) or on_segment(pt, a, b)):
                    return True
            return False

        dead_w = [w for w, (a, b) in segs if not connected(a, w) or not connected(b, w)]
        dead_l = [l for l in labels if not any(on_segment(P(first(l, 'at')), a, b) for _w, (a, b) in segs)
                  and P(first(l, 'at')) not in pin_pts]
        # power symbols (GND, +3V3, ...) and no-connect flags that no longer touch anything
        ends = {p for _w, ab in segs for p in ab}
        dead_p = []
        for c in sch:
            if isinstance(c, list) and c[0] == 'symbol' and str(first(c, 'lib_id')[1]).startswith(('power:', 'RPI - Power:')):
                pt = pins.get((ref_of(c), '1'))
                if pt and not (pt in ends or any(on_segment(pt, a, b) for _w, (a, b) in segs)
                               or sum(1 for v in pin_pts if v == pt) > 1):
                    dead_p.append(c)
            if isinstance(c, list) and c[0] == 'no_connect':
                if P(first(c, 'at')) not in pin_pts:
                    dead_p.append(c)
        dead_l += dead_p
        if not dead_w and not dead_l:
            break
        dead = {id(x) for x in dead_w + dead_l}
        sch[:] = [c for c in sch if id(c) not in dead]

    # unused GPIO labels: label + stub -> no-connect on the pin; used ones -> global labels
    wires = [c for c in sch if isinstance(c, list) and c[0] == 'wire']
    out, removed = [], set()
    for c in sch:
        if isinstance(c, list) and c[0] == 'label':
            name = str(c[1])
            if name in GLOBAL:
                at = first(c, 'at')
                g = ['global_label', Str(name), ['shape', 'passive'], at, ['fields_autoplaced', 'yes'],
                     first(c, 'effects'), first(c, 'uuid'),
                     ['property', Str('Intersheetrefs'), Str('${INTERSHEET_REFS}'), at,
                      ['effects', ['font', ['size', 1.27, 1.27]], ['hide', 'yes']]]]
                out.append(g)
                continue
            if name.startswith('GPIO') or name in ('SWCLK', 'SWD'):    # unused: no pads on rev A
                lp = P(first(c, 'at'))
                for w in wires:
                    a, b = [P(xy) for xy in find(first(w, 'pts'), 'xy')]
                    if lp in (a, b):
                        other = b if lp == a else a
                        if other in pin_pts:
                            removed.add(id(w))
                            out.append(['no_connect', ['at', other[0], other[1]], ['uuid', U()]])
                            break
                else:
                    out.append(c)    # label not on a stub: keep
                continue
        out.append(c)
    sch[:] = [c for c in out if id(c) not in removed]

    for c in sch:
        if not (isinstance(c, list) and c[0] == 'symbol' and first(c, 'lib_id') is not None):
            continue
        ref = ref_of(c)
        if ref in NOT_PARTS:
            ib = first(c, 'in_bom')
            if ib is not None:
                ib[1] = 'no'
        if ref not in LCSC:
            continue
        value, lcsc = LCSC[ref]
        props = [p for p in find(c, 'property')]
        if value:
            next(p for p in props if p[1] == 'Value')[2] = Str(value)
        old = next((p for p in props if p[1] == 'LCSC'), None)
        if old is not None:
            old[2] = Str(lcsc)
        else:
            ds = next(p for p in props if p[1] == 'Datasheet')
            new = [x for x in ds]
            new[1], new[2] = Str('LCSC'), Str(lcsc)
            new = [x for x in new if not (isinstance(x, list) and x and x[0] == 'uuid')]
            c.insert(c.index(ds) + 1, new)
    open(dst, 'w').write(dump(sch) + '\n')
    print(f'removed {sorted(REMOVE)}; wrote {dst}')


if __name__ == '__main__':
    main(sys.argv[1], sys.argv[2])
